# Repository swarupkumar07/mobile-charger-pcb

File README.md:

# Mobile Charger PCB

Custom PCB design for a mobile charger providing stable and efficient power output.

## Description

This project is a mobile charger PCB designed to convert input power into a stable DC output for charging mobile devices. The design is compact and optimized for efficient performance.

## Features

* Stable output voltage
* Compact PCB layout
* Efficient power conversion
* Reliable design

## Files Included

* Schematic file
* PCB layout file
* Gerber files
* Bill of Materials (BOM)

## Tools Used

* KiCad / Eagle

## Preview

images 

## Usage

Use the Gerber files to manufacture the PCB or modify the design as needed.

## License

Free to use for learning and personal projects.

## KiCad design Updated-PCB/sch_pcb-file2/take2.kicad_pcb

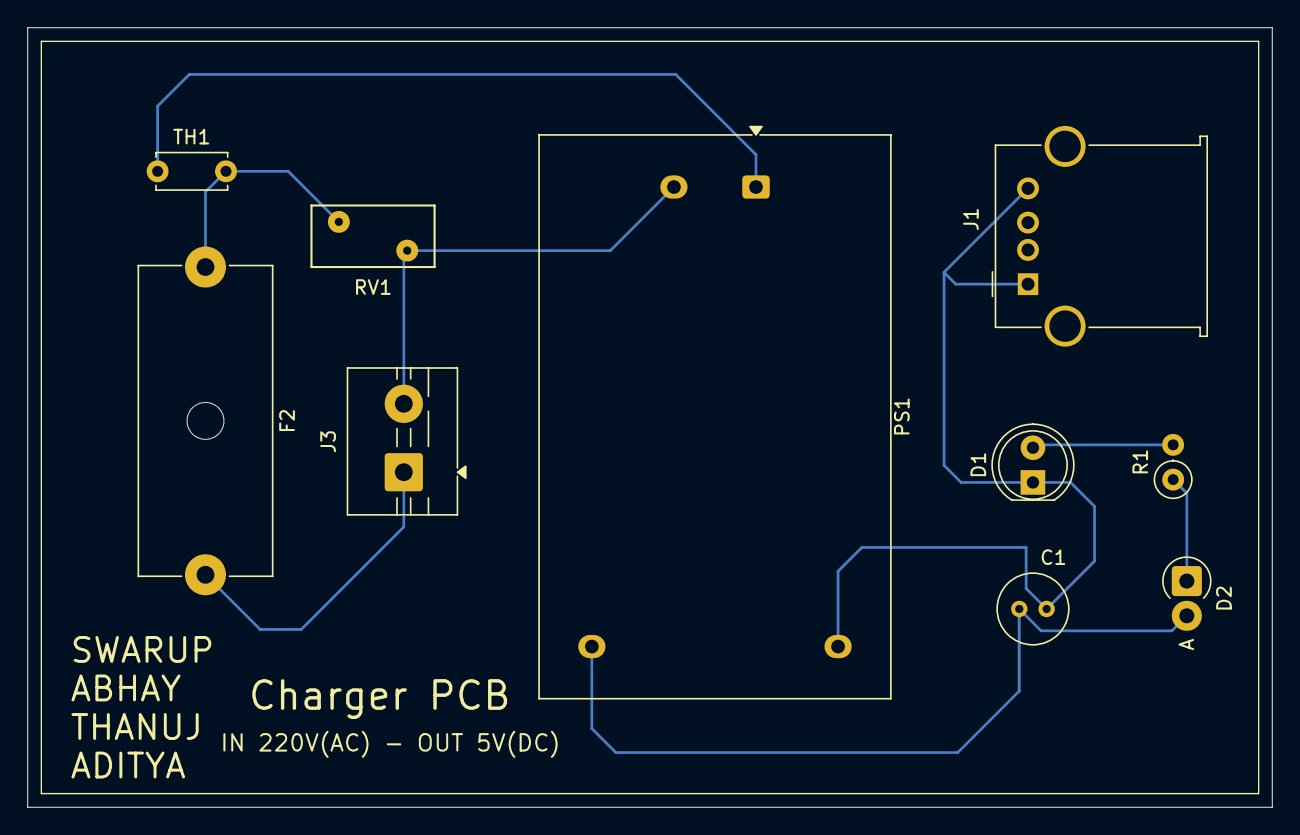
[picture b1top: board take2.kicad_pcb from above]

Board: 2 copper layers, 91.0 x 57.0 mm, 10 parts (0 on the bottom side), 8 nets.

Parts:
C1: C; C_Radial_D5.0mm_H5.0mm_P2.00mm
D1: LED; LED_D5.0mm
D2: D; D_DO-41_SOD81_P2.54mm_Vertical_AnodeUp
F2: Fuse; Fuseholder_Cylinder-5x20mm_Schurter_0031_8201_Horizontal_Op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
J1: USB_A; USB_A_Molex_67643_Horizontal
J3: Conn_01x02; TerminalBlock_MaiXu_MX126-5.0-02P_1x02_P5.00mm
PS1: HLK-5M05; Converter_ACDC_Hi-Link_HLK-5Mxx
R1: R; R_Axial_DIN0207_L6.3mm_D2.5mm_P2.54mm_Vertical
RV1: Varistor; RV_Disc_D9mm_W4.5mm_P5mm
TH1: Thermistor_NTC; C_Disc_D5.0mm_W2.5mm_P5.00mm

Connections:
/L: F2.2, J3.1
/N: J3.2, PS1.2 (AC/N), RV1.2
unnamed: D1.2 (A), R1.2
unnamed: C1.2, D1.1 (K), J1.1 (VBUS), J1.4 (GND), PS1.3 (-Vout)
unnamed: C1.1, D2.2 (A), PS1.4 (+Vout)
unnamed: D2.1 (K), R1.1
unnamed: F2.1, RV1.1, TH1.2
unnamed: PS1.1 (AC/L), TH1.1

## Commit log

2026-04-08 Create DesignFiles
2026-04-09 Add files via upload
    This Updated PCB is made using AC-DC Module ( HLK-5M05 ) to reduce a complex circuit to a simple and clear understandable circuit
